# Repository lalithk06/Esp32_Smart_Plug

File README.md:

# ⚡ ESP32 Smart Plug — Hardware Reference Design
*A compact and efficient smart plug built around the ESP32-S3 for intelligent power control, protection, and connectivity.*

This project presents the schematic and PCB design of a smart plug capable of switching AC loads while supporting modern embedded features such as USB connectivity, RTC support, and protection circuitry. Designed to explore real-world embedded hardware development and PCB design practices.

> 📺 This project was developed by following a YouTube playlist by **Ampnics**, with additional learning and implementation.

---

## ⚙ Working Principle

* The system uses an **ESP32-S3 microcontroller** as the core processing unit.
* AC mains input is stepped down and regulated to provide safe DC power for the controller.
* A **relay switching circuit** enables the ESP32 to control connected appliances.
* Protection components safeguard the device against voltage spikes and electrical faults.
* USB connectivity allows programming and debugging.
* RTC support enables future time-based automation features.

---

## 📌 Objective
To design and develop a reliable hardware platform for a smart plug that demonstrates safe mains power handling, embedded control, and scalable architecture for future IoT-based automation.

---

## ⚙ Components Used

| No. | Components              | Specifications / Role |
| :---: | :-----------------------: | :--------------------: |
| 1. | ESP32-S3 Module | Main microcontroller with Wi-Fi & BLE |
| 2. | Relay | AC load switching |
| 3. | AC-DC Power Module | Converts mains to regulated DC |
| 4. | Voltage Regulators | Stable voltage supply |
| 5. | Protection Circuitry | Fuse, MOV, flyback diode, etc. |
| 6. | USB Interface | Programming & debugging |
| 7. | Capacitors & Resistors | Filtering and biasing |
| 8. | RTC (Optional) | Time-based control support |

---

## 📷 Preview

### 🖼 Schematic Diagram  
<div align="center">
  
</div>

### 📐 PCB Layout  
<div align="center">
  
</div>

### 🧊 3D View  
<div align="center">
  
</div>

---

## 🧠 Design Highlights

- Proper isolation between AC mains and low-voltage sections  
- Dedicated power zoning for noise reduction  
- Flyback protection for relay reliability  
- USB interface for easy firmware flashing  

---

## ⚠ Safety Considerations

- Isolation maintained between high-voltage and low-voltage domains  
- Proper creepage and clearance followed  
- Fuse and MOV used for protection  
- Designed for educational and prototyping purposes only  

---

## 📊 Specifications

| Parameter | Value |
|----------|------|
| Input Voltage | 230V AC |
| Output Control | Relay-based switching |
| MCU | ESP32-S3 |
| Communication | Wi-Fi, BLE |

---

## 🚀 Key Highlights

✅ Designed with real-world electrical safety considerations  
✅ Suitable for home automation applications  
✅ Expandable for IoT integration  
✅ Compact PCB layout  
✅ Industry-relevant hardware design workflow  

---

## 🔄 Future Improvements

- Energy monitoring (current & voltage sensing)  
- Mobile app / cloud integration  
- Overload and thermal protection  
- Smart scheduling and automation  
- Voice assistant compatibility  
- Custom enclosure design  
- Power consumption optimization  

---

⭐ *This project is part of my learning journey in hardware design and PCB development.*

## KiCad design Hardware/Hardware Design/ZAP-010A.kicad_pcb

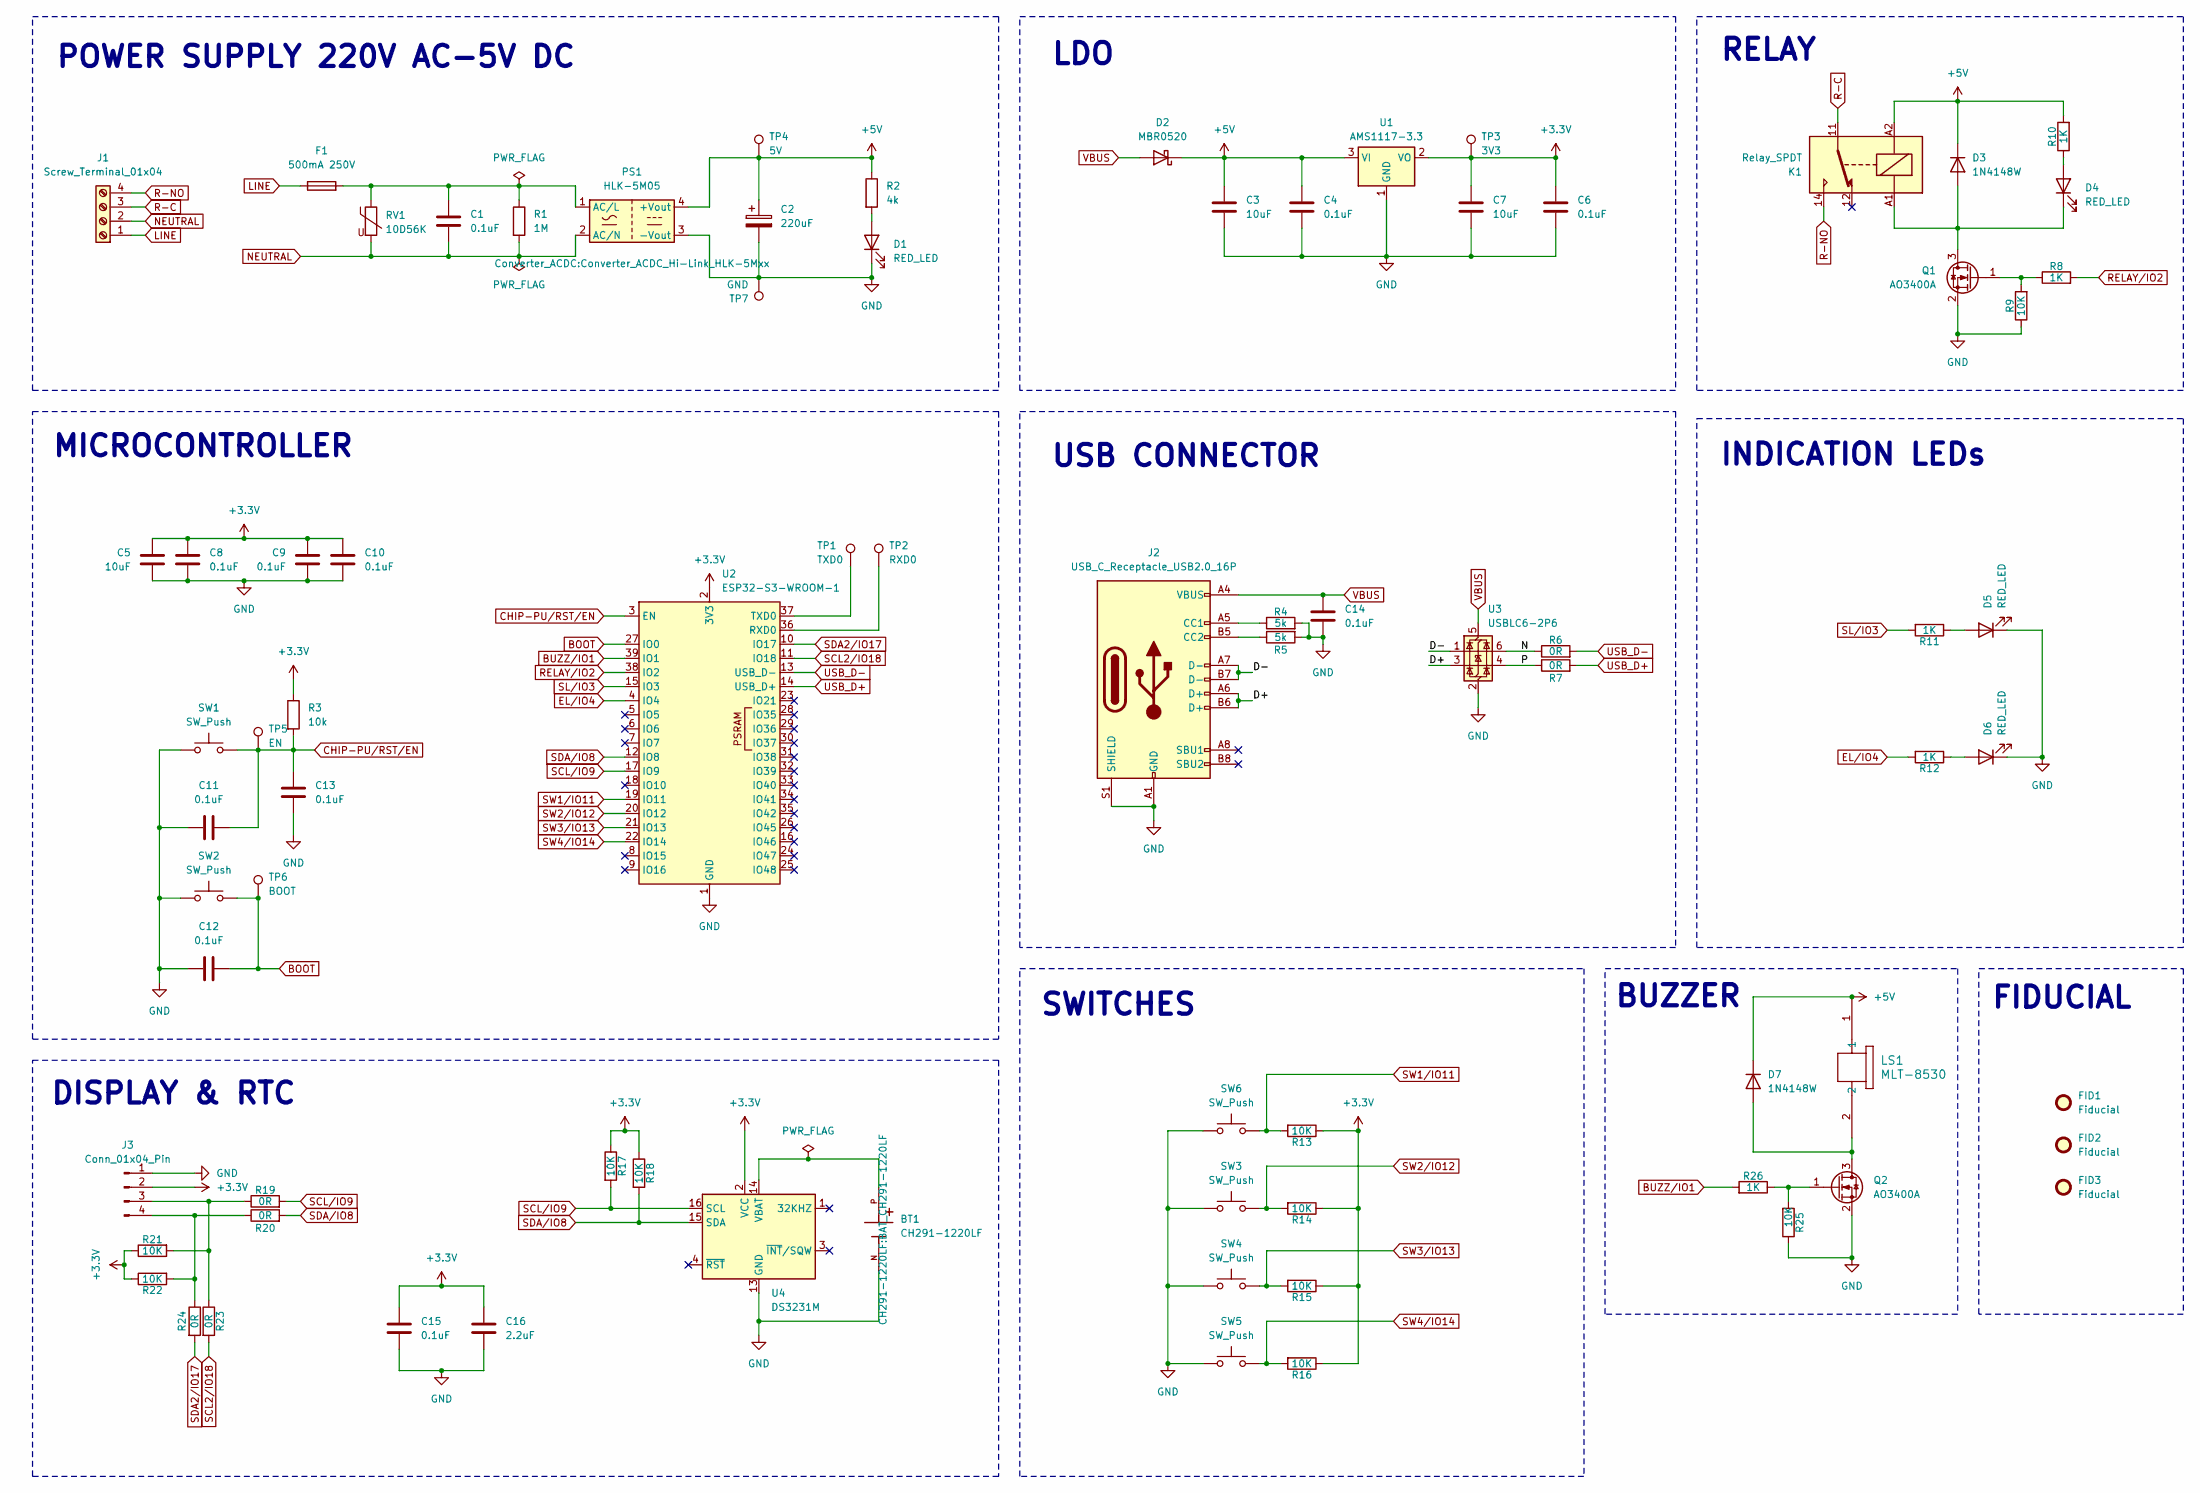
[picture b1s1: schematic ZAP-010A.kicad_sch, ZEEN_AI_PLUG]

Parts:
BT1: CH291-1220LF; BAT_CH291-1220LF; PARTREV A
C1: 0.1uF; C_Rect_L13.0mm_W6.0mm_P10.00mm_FKS3_FKP3_MKS4
C2: 220uF; CP_Elec_8x10
C3, C5, C7: 10uF; C_0805_2012Metric
C4, C6, C8, C9, C10, C11, C12, C13, C14, C15: 0.1uF; C_0603_1608Metric
C16: 2.2uF; C_0805_2012Metric
D1, D5, D6: RED_LED; LED_D3.0mm
D2: MBR0520; D_SOD-123
D3, D7: 1N4148W; D_SOD-123
D4: RED_LED; LED_0603_1608Metric_Pad1.05x0.95mm_HandSolder
F1: 500mA 250V; Fuse_Littelfuse_395Series
FID1, FID2, FID3: Fiducial; Fiducial_0.75mm_Mask1.5mm
J1: Screw_Terminal_01x04; TerminalBlock_MaiXu_MX126-5.0-04P_1x04_P5.00mm
J2: USB_C_Receptacle_USB2.0_16P; USB_C_Receptacle_HCTL_HC-TYPE-C-16P-01A
J3: Conn_01x04_Pin; PinHeader_1x04_P2.54mm_Vertical
K1: Relay_SPDT; Relay_SPDT_Hongfa_HF3F-L-xx-1ZL1T
LS1: MLT-8530; MLT-8530_JHE
PS1: HLK-5M05; Converter_ACDC_Hi-Link_HLK-5Mxx
Q1, Q2: AO3400A; SOT-23
R1: 1M; R_Axial_DIN0204_L3.6mm_D1.6mm_P5.08mm_Horizontal
R2: 4k; R_0603_1608Metric
R3: 10k; R_0603_1608Metric
R4, R5: 5k; R_0603_1608Metric
R6, R7, R19, R20, R23, R24: 0R; R_0603_1608Metric
R8, R10, R11, R12, R26: 1K; R_0603_1608Metric
R9, R13, R14, R15, R16, R17, R18, R21, R22, R25: 10K; R_0603_1608Metric
RV1: 10D56K; RV_Disc_D12mm_W5.8mm_P7.5mm
SW1, SW3, SW4, SW5, SW6: SW_Push; SW_PUSH_6mm
SW2: SW_Push; SW_Push_SPST_NO_Alps_SKRK
TP1: TXD0; TestPoint_Pad_D2.5mm
TP2: RXD0; TestPoint_Pad_D2.5mm
TP3: 3V3; TestPoint_Pad_D2.5mm
TP4: 5V; TestPoint_Pad_D2.5mm
TP5: EN; TestPoint_Pad_D2.5mm
TP6: BOOT; TestPoint_Pad_D2.5mm
TP7: GND; TestPoint_Pad_D2.5mm
U1: AMS1117-3.3; SOT-223-3_TabPin2
U2: ESP32-S3-WROOM-1
U3: USBLC6-2P6; SOT-666
U4: DS3231M; SOIC-16W_7.5x10.3mm_P1.27mm

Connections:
+3.3V: C5.1, C6.1, C7.1, C8.1, C9.1, C10.1, C15.2, C16.2, J3.2, R3.1, R13.1, R14.1, R15.1, R16.1, R17.1, R18.1, R21.1, R22.1, TP3.1, U1.2 (VO), U2.2 (3V3), U4.2 (VCC)
+5V: C2.1, C3.1, C4.1, D2.1 (K), D3.1 (K), D7.1 (K), K1.A2, LS1.1, PS1.4 (+Vout), R2.1, R10.2, TP4.1, U1.3 (VI)
/D+: J2.A6 (D+), J2.B6 (D+), U3.3 (I/O2)
/D-: J2.A7 (D-), J2.B7 (D-), U3.1 (I/O1)
/N: R6.1, U3.6 (I/O1)
/P: R7.1, U3.4 (I/O2)
BOOT: C12.2, SW2.2, TP6.1, U2.27 (IO0)
BUZZ/IO1: R26.2, U2.39 (IO1)
CHIP-PU/RST/EN: C11.2, C13.1, R3.2, SW1.2, TP5.1, U2.3 (EN)
EL/IO4: R12.2, U2.4 (IO4)
GND: BT1.N, C2.2, C3.2, C4.2, C5.2, C6.2, C7.2, C8.2, C9.2, C10.2, C11.1, C12.1, C13.2, C14.2, C15.1, C16.1, D1.1 (K), D5.1 (K), D6.1 (K), J2.A1 (GND), J2.A12 (GND), J2.B1 (GND), J2.B12 (GND), J2.S1 (SHIELD), J3.1, PS1.3 (-Vout), Q1.2 (S), Q2.2 (S), R4.2, R5.2, R9.1, R25.1, SW1.1, SW2.1, SW3.1, SW4.1, SW5.1, SW6.1, TP7.1, U1.1 (GND), U2.1 (GND), U2.40 (GND), U2.41 (GND), U3.2 (GND), U4.5 (GND), U4.6 (GND), U4.7 (GND), U4.8 (GND), U4.9 (GND), U4.10 (GND), U4.11 (GND), U4.12 (GND), U4.13 (GND)
LINE: F1.1, J1.1
NEUTRAL: C1.2, J1.2, PS1.2 (AC/N), R1.2, RV1.2
unnamed: D1.2 (A), R2.2
unnamed: D3.2 (A), D4.1 (K), K1.A1, Q1.3 (D)
unnamed: D4.2 (A), R10.1
unnamed: D5.2 (A), R11.1
unnamed: D6.2 (A), R12.1
unnamed: D7.2 (A), LS1.2, Q2.3 (D)
unnamed: J2.A5 (CC1), R4.1
unnamed: J2.B5 (CC2), R5.1
unnamed: J3.3, R19.1, R21.2, R23.1
unnamed: J3.4, R20.1, R22.2, R24.1
unnamed: C1.1, F1.2, PS1.1 (AC/L), R1.1, RV1.1
unnamed: Q1.1 (G), R8.1, R9.2
unnamed: Q2.1 (G), R25.2, R26.1
unnamed: TP2.1, U2.36 (RXD0)
unnamed: TP1.1, U2.37 (TXD0)
unnamed: BT1.P, U4.14 (VBAT)
R-C: J1.3, K1.11
R-NO: J1.4, K1.14
RELAY/IO2: R8.2, U2.38 (IO2)
SCL2/IO18: R23.2, U2.11 (IO18)
SCL/IO9: R17.2, R19.2, U2.17 (IO9), U4.16 (SCL)
SDA2/IO17: R24.2, U2.10 (IO17)
SDA/IO8: R18.2, R20.2, U2.12 (IO8), U4.15 (SDA)
SL/IO3: R11.2, U2.15 (IO3)
SW1/IO11: R13.2, SW6.2, U2.19 (IO11)
SW2/IO12: R14.2, SW3.2, U2.20 (IO12)
SW3/IO13: R15.2, SW4.2, U2.21 (IO13)
SW4/IO14: R16.2, SW5.2, U2.22 (IO14)
USB_D+: R7.2, U2.14 (USB_D+)
USB_D-: R6.2, U2.13 (USB_D-)
VBUS: C14.1, D2.2 (A), J2.A4 (VBUS), J2.A9 (VBUS), J2.B4 (VBUS), J2.B9 (VBUS), U3.5 (VBUS)

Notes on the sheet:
DISPLAY & RTC
MICROCONTROLLER
LDO
FIDUCIAL
POWER SUPPLY 220V AC-5V DC
BUZZER
INDICATION LEDs
SWITCHES
USB CONNECTOR
RELAY

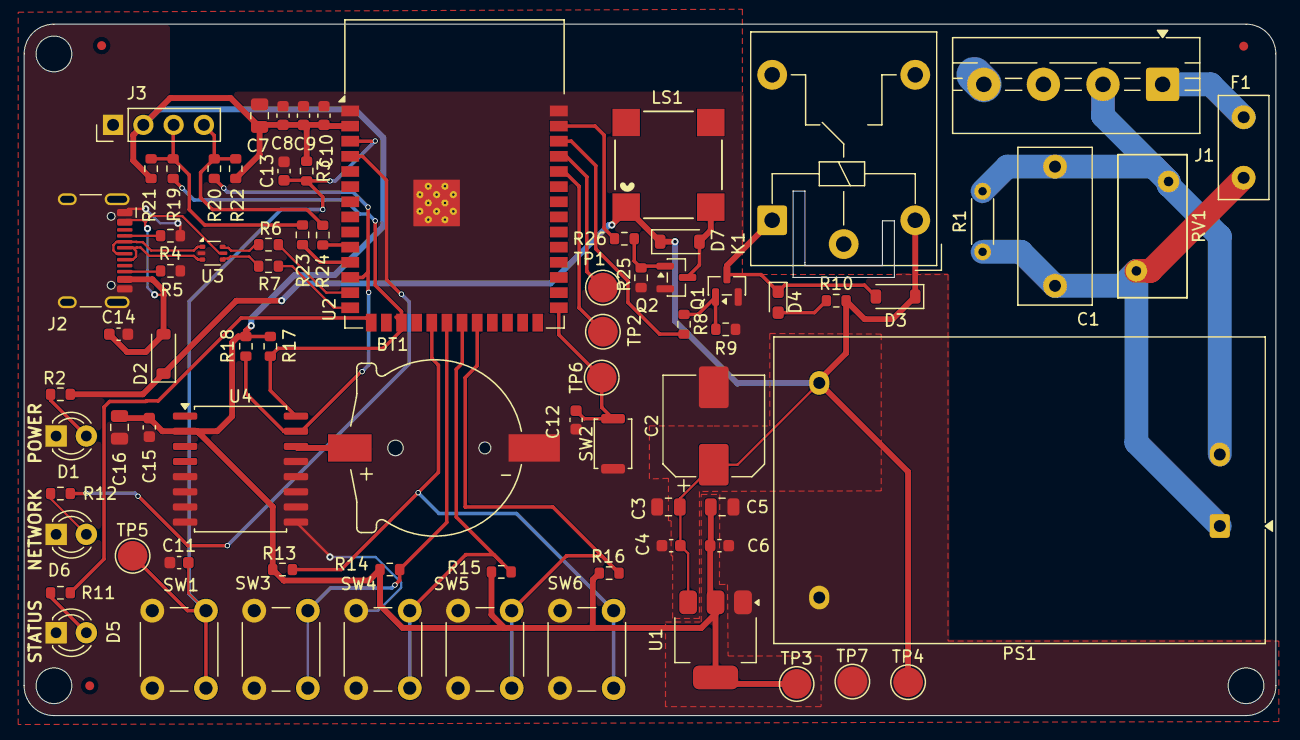
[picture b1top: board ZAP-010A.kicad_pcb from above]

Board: 2 copper layers, 105.0 x 58.0 mm, 80 parts (0 on the bottom side), 44 nets.

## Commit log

2026-02-02 Added README
2026-02-02 Renamed folder
2026-02-02 renamed file
2026-02-15 PCB edited
2026-03-13 PCB layout and arrangements are done
2026-03-13 Routing
2026-03-13 Routing completed
2026-03-14 ERC and DRC done
2026-04-11 DRC errors cleared
2026-04-11 3D model added
2026-04-11 Manufacturing Files generated
2026-04-13 Images added
2026-04-13 .gitignore added
2026-04-13 Ignored certtain files
2026-04-13 Ignore file modified
2026-04-13 Removed ignored folders from tracking
2026-04-13 README optimised
2026-04-13 README updated
2026-04-15 Charging module and buck converetr added
